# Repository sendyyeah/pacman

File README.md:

# pacman
40% Ortholinear Keyboard based on Raspberry RP2040

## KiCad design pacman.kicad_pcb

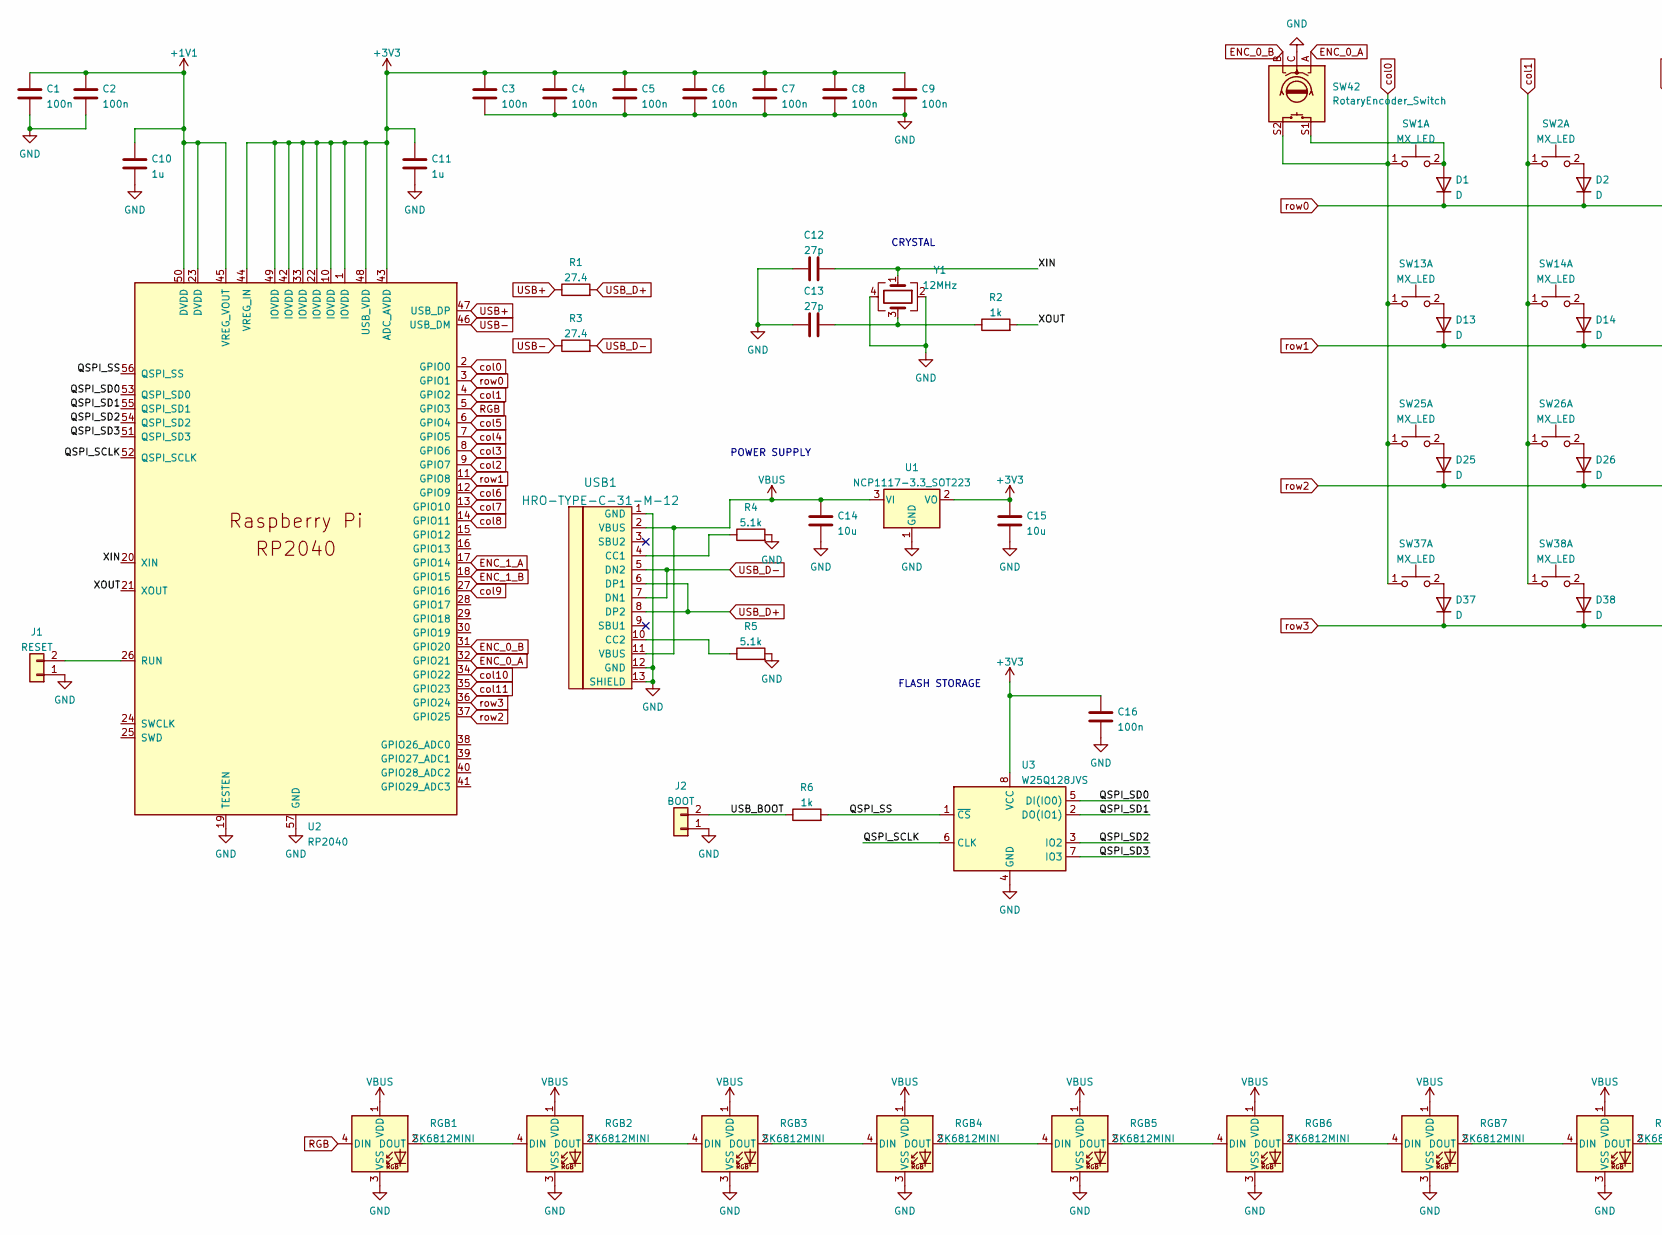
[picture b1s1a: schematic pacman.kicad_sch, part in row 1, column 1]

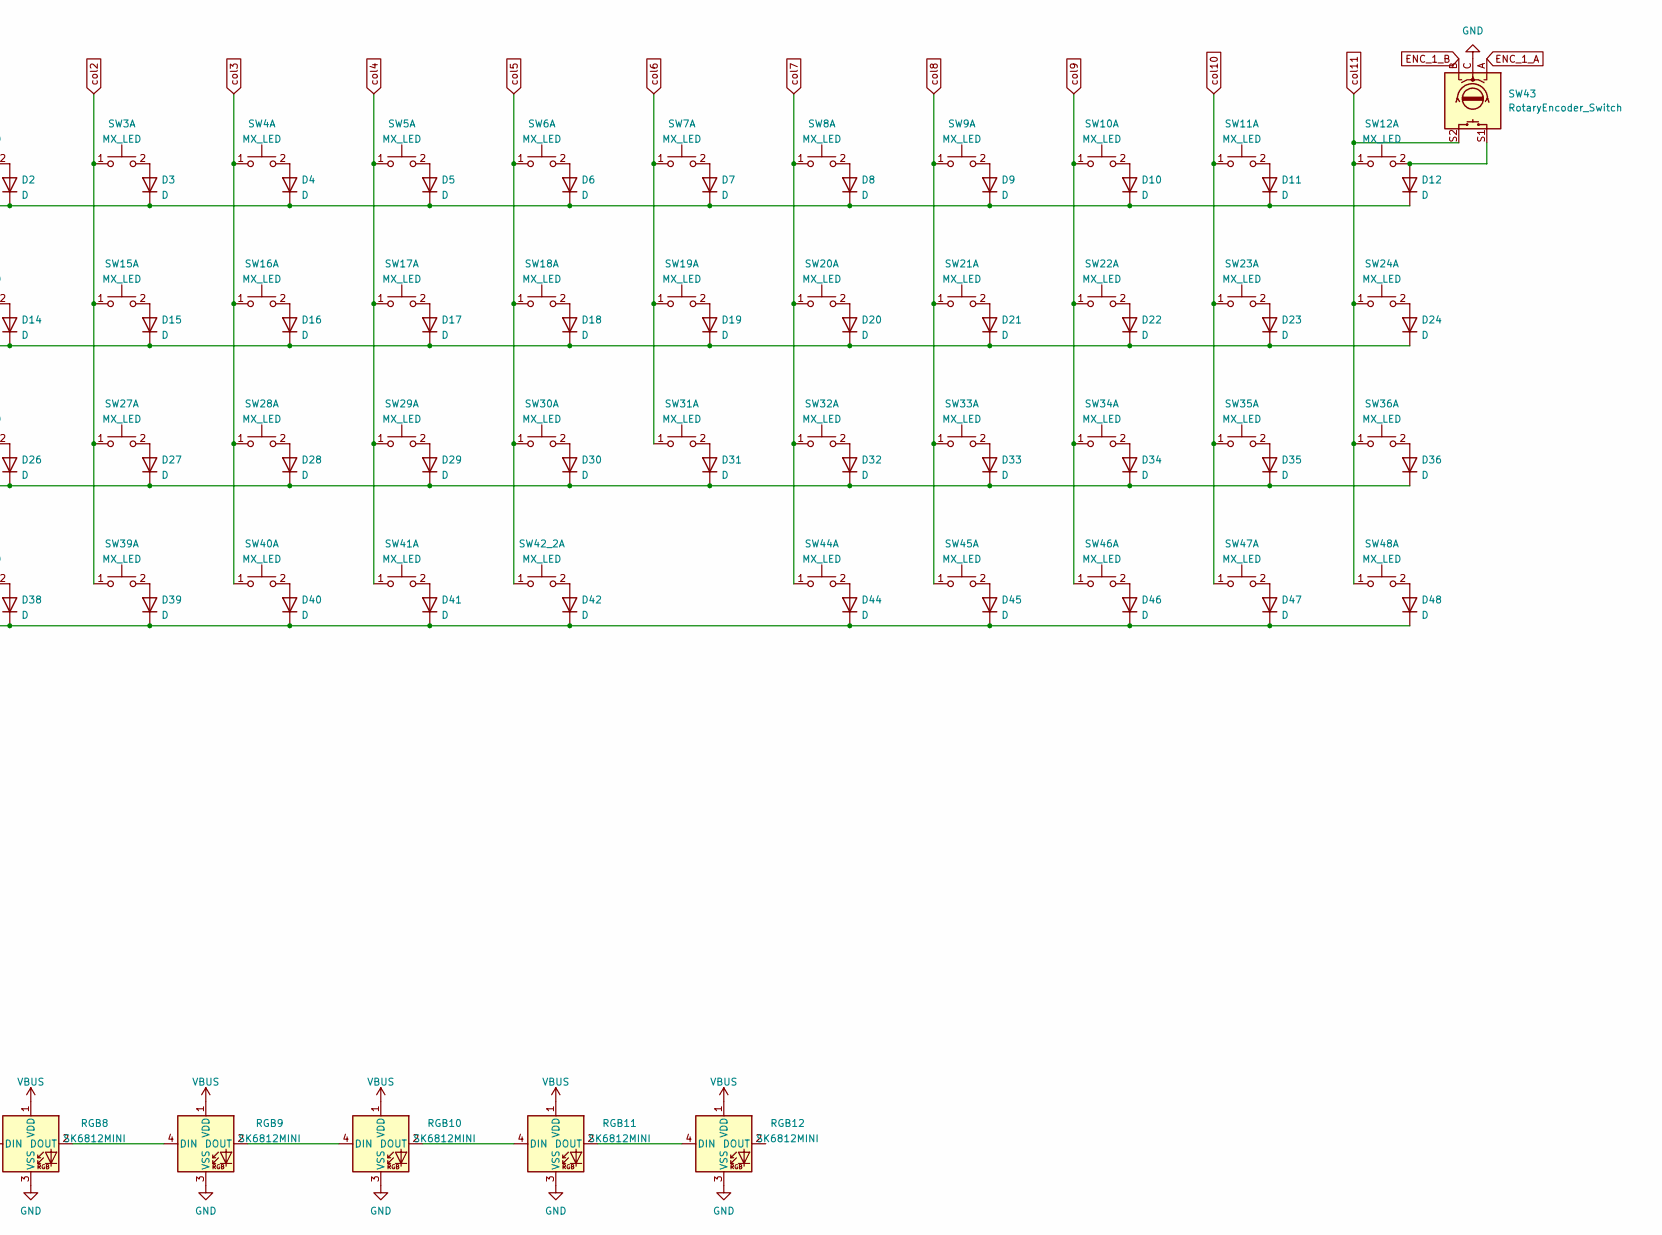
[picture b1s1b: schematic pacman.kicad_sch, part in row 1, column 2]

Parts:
C1, C2, C3, C4, C5, C6, C7, C8, C9, C16: 100n; C_0402_1005Metric
C10, C11: 1u; C_0402_1005Metric
C12, C13: 27p; C_0402_1005Metric
C14, C15: 10u; C_0402_1005Metric
D1, D2, D3, D4, D5, D6, D7, D8, D9, D10, D11, D12, D13, D14, D15, D16, D17, D18, D19, D20, D21, D22, D23, D24, D25, D26, D27, D28, D29, D30, D31, D32, D33, D34, D35, D36, D37, D38, D39, D40, D41, D42, D44, D45, D46, D47, D48: D; D_SOD-323
J1: RESET; SW_SPST_TL3342
J2: BOOT; SW_SPST_TL3342
R1, R3: 27.4; R_0402_1005Metric
R2, R6: 1k; R_0402_1005Metric
R4, R5: 5.1k; R_0402_1005Metric
RGB1, RGB2, RGB3, RGB4, RGB5, RGB6, RGB7, RGB8, RGB9, RGB10, RGB11, RGB12: SK6812MINI; LED_WS2812B_PLCC4_5.0x5.0mm_P3.2mm
SW1, SW2, SW3, SW4, SW5, SW6, SW7, SW8, SW9, SW10, SW11, SW12, SW13, SW14, SW15, SW16, SW17, SW18, SW19, SW20, SW21, SW22, SW23, SW24, SW25, SW26, SW27, SW28, SW29, SW30, SW31, SW32, SW33, SW34, SW35, SW36, SW37, SW38, SW39, SW40, SW41, SW44, SW45, SW46, SW47, SW48: MX_LED; MXOnly-1U-Hotswap
SW42, SW43: RotaryEncoder_Switch; RotaryEncoder_EC11
SW42_2: MX_LED; MXOnly-2U-Hotswap-ReversedStabilizers
U1: NCP1117-3.3_SOT223; SOT-223-3_TabPin2
U2: RP2040; RP2040-QFN-56
U3: W25Q128JVS; SOIC-8_5.23x5.23mm_P1.27mm
USB1: HRO-TYPE-C-31-M-12; HRO-TYPE-C-31-M-12-Assembly
Y1: 12MHz; Crystal_SMD_3225-4Pin_3.2x2.5mm_HandSoldering

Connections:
+1V1: C1.1, C2.1, C10.1, U2.23 (DVDD), U2.45 (VREG_VOUT), U2.50 (DVDD)
+3V3: C3.1, C4.1, C5.1, C6.1, C7.1, C8.1, C9.1, C11.1, C15.1, C16.1, U1.2 (VO), U2.1 (IOVDD), U2.10 (IOVDD), U2.22 (IOVDD), U2.33 (IOVDD), U2.42 (IOVDD), U2.43 (ADC_AVDD), U2.44 (VREG_IN), U2.48 (USB_VDD), U2.49 (IOVDD), U3.8 (VCC)
/QSPI_SCLK: U2.52 (QSPI_SCLK), U3.6 (CLK)
/QSPI_SD0: U2.53 (QSPI_SD0), U3.5 (DI(IO0))
/QSPI_SD1: U2.55 (QSPI_SD1), U3.2 (DO(IO1))
/QSPI_SD2: U2.54 (QSPI_SD2), U3.3 (IO2)
/QSPI_SD3: U2.51 (QSPI_SD3), U3.7 (IO3)
/QSPI_SS: R6.2, U2.56 (QSPI_SS), U3.1 (~CS)
/USB_BOOT: J2.2, R6.1
/XIN: C12.2, U2.20 (XIN), Y1.1
/XOUT: R2.2, U2.21 (XOUT)
ENC_0_A: SW42.A, U2.32 (GPIO21)
ENC_0_B: SW42.B, U2.31 (GPIO20)
ENC_1_A: SW43.A, U2.17 (GPIO14)
ENC_1_B: SW43.B, U2.18 (GPIO15)
GND: C1.2, C2.2, C3.2, C4.2, C5.2, C6.2, C7.2, C8.2, C9.2, C10.2, C11.2, C12.1, C13.1, C14.2, C15.2, C16.2, J1.1, J2.1, R4.2, R5.2, RGB1.3 (VSS), RGB2.3 (VSS), RGB3.3 (VSS), RGB4.3 (VSS), RGB5.3 (VSS), RGB6.3 (VSS), RGB7.3 (VSS), RGB8.3 (VSS), RGB9.3 (VSS), RGB10.3 (VSS), RGB11.3 (VSS), RGB12.3 (VSS), SW42.C, SW43.C, U1.1 (GND), U2.19 (TESTEN), U2.57 (GND), U3.4 (GND), USB1.1 (GND), USB1.12 (GND), USB1.13 (SHIELD), Y1.2, Y1.4
unnamed: C13.2, R2.1, Y1.3
unnamed: D1.2 (A), SW1.2, SW42.S1
unnamed: D2.2 (A), SW2.2
unnamed: D3.2 (A), SW3.2
unnamed: D4.2 (A), SW4.2
unnamed: D5.2 (A), SW5.2
unnamed: D6.2 (A), SW6.2
unnamed: D7.2 (A), SW7.2
unnamed: D8.2 (A), SW8.2
unnamed: D9.2 (A), SW9.2
unnamed: D10.2 (A), SW10.2
unnamed: D11.2 (A), SW11.2
unnamed: D12.2 (A), SW12.2, SW43.S1
unnamed: D13.2 (A), SW13.2
unnamed: D14.2 (A), SW14.2
unnamed: D15.2 (A), SW15.2
unnamed: D16.2 (A), SW16.2
unnamed: D17.2 (A), SW17.2
unnamed: D18.2 (A), SW18.2
unnamed: D19.2 (A), SW19.2
unnamed: D20.2 (A), SW20.2
unnamed: D21.2 (A), SW21.2
unnamed: D22.2 (A), SW22.2
unnamed: D23.2 (A), SW23.2
unnamed: D24.2 (A), SW24.2
unnamed: D25.2 (A), SW25.2
unnamed: D26.2 (A), SW26.2
unnamed: D27.2 (A), SW27.2
unnamed: D28.2 (A), SW28.2
unnamed: D29.2 (A), SW29.2
unnamed: D30.2 (A), SW30.2
unnamed: D31.2 (A), SW31.2
unnamed: D32.2 (A), SW32.2
unnamed: D33.2 (A), SW33.2
unnamed: D34.2 (A), SW34.2
unnamed: D35.2 (A), SW35.2
unnamed: D36.2 (A), SW36.2
unnamed: D37.2 (A), SW37.2
unnamed: D38.2 (A), SW38.2
unnamed: D39.2 (A), SW39.2
unnamed: D40.2 (A), SW40.2
unnamed: D41.2 (A), SW41.2
unnamed: D42.2 (A), SW42_2.2
unnamed: D44.2 (A), SW44.2
unnamed: D45.2 (A), SW45.2
unnamed: D46.2 (A), SW46.2
unnamed: D47.2 (A), SW47.2
unnamed: D48.2 (A), SW48.2
unnamed: J1.2, U2.26 (RUN)
unnamed: RGB1.2 (DOUT), RGB2.4 (DIN)
unnamed: RGB2.2 (DOUT), RGB3.4 (DIN)
unnamed: RGB3.2 (DOUT), RGB4.4 (DIN)
unnamed: RGB4.2 (DOUT), RGB5.4 (DIN)
unnamed: RGB5.2 (DOUT), RGB6.4 (DIN)
unnamed: RGB6.2 (DOUT), RGB7.4 (DIN)
unnamed: RGB7.2 (DOUT), RGB8.4 (DIN)
unnamed: RGB8.2 (DOUT), RGB9.4 (DIN)
unnamed: RGB9.2 (DOUT), RGB10.4 (DIN)
unnamed: RGB10.2 (DOUT), RGB11.4 (DIN)
unnamed: RGB11.2 (DOUT), RGB12.4 (DIN)
unnamed: R4.1, USB1.4 (CC1)
unnamed: R5.1, USB1.10 (CC2)
RGB: RGB1.4 (DIN), U2.5 (GPIO3)
USB+: R1.1, U2.47 (USB_DP)
USB-: R3.1, U2.46 (USB_DM)
USB_D+: R1.2, USB1.6 (DP1), USB1.8 (DP2)
USB_D-: R3.2, USB1.5 (DN2), USB1.7 (DN1)
VBUS: C14.1, RGB1.1 (VDD), RGB2.1 (VDD), RGB3.1 (VDD), RGB4.1 (VDD), RGB5.1 (VDD), RGB6.1 (VDD), RGB7.1 (VDD), RGB8.1 (VDD), RGB9.1 (VDD), RGB10.1 (VDD), RGB11.1 (VDD), RGB12.1 (VDD), U1.3 (VI), USB1.2 (VBUS), USB1.11 (VBUS)
col0: SW1.1, SW13.1, SW25.1, SW37.1, SW42.S2, U2.2 (GPIO0)
col1: SW2.1, SW14.1, SW26.1, SW38.1, U2.4 (GPIO2)
col2: SW3.1, SW15.1, SW27.1, SW39.1, U2.9 (GPIO7)
col3: SW4.1, SW16.1, SW28.1, SW40.1, U2.8 (GPIO6)
col4: SW5.1, SW17.1, SW29.1, SW41.1, U2.7 (GPIO5)
col5: SW6.1, SW18.1, SW30.1, SW42_2.1, U2.6 (GPIO4)
col6: SW7.1, SW19.1, SW31.1, U2.12 (GPIO9)
col7: SW8.1, SW20.1, SW32.1, SW44.1, U2.13 (GPIO10)
col8: SW9.1, SW21.1, SW33.1, SW45.1, U2.14 (GPIO11)
col9: SW10.1, SW22.1, SW34.1, SW46.1, U2.27 (GPIO16)
col10: SW11.1, SW23.1, SW35.1, SW47.1, U2.34 (GPIO22)
col11: SW12.1, SW24.1, SW36.1, SW43.S2, SW48.1, U2.35 (GPIO23)
row0: D1.1 (K), D2.1 (K), D3.1 (K), D4.1 (K), D5.1 (K), D6.1 (K), D7.1 (K), D8.1 (K), D9.1 (K), D10.1 (K), D11.1 (K), D12.1 (K), U2.3 (GPIO1)
row1: D13.1 (K), D14.1 (K), D15.1 (K), D16.1 (K), D17.1 (K), D18.1 (K), D19.1 (K), D20.1 (K), D21.1 (K), D22.1 (K), D23.1 (K), D24.1 (K), U2.11 (GPIO8)
row2: D25.1 (K), D26.1 (K), D27.1 (K), D28.1 (K), D29.1 (K), D30.1 (K), D31.1 (K), D32.1 (K), D33.1 (K), D34.1 (K), D35.1 (K), D36.1 (K), U2.37 (GPIO25)
row3: D37.1 (K), D38.1 (K), D39.1 (K), D40.1 (K), D41.1 (K), D42.1 (K), D44.1 (K), D45.1 (K), D46.1 (K), D47.1 (K), D48.1 (K), U2.36 (GPIO24)

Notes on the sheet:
CRYSTAL
FLASH STORAGE
POWER SUPPLY

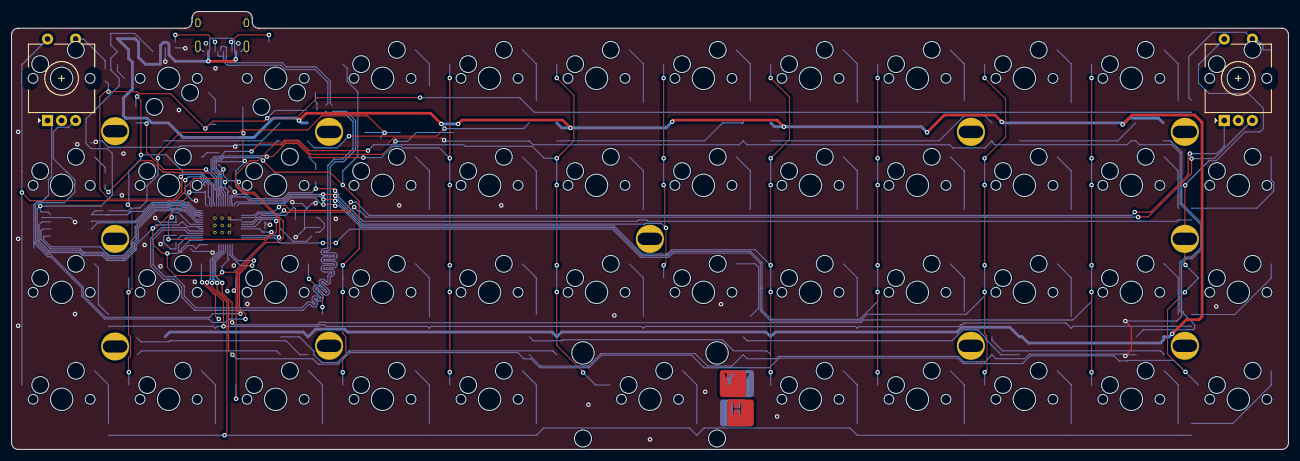
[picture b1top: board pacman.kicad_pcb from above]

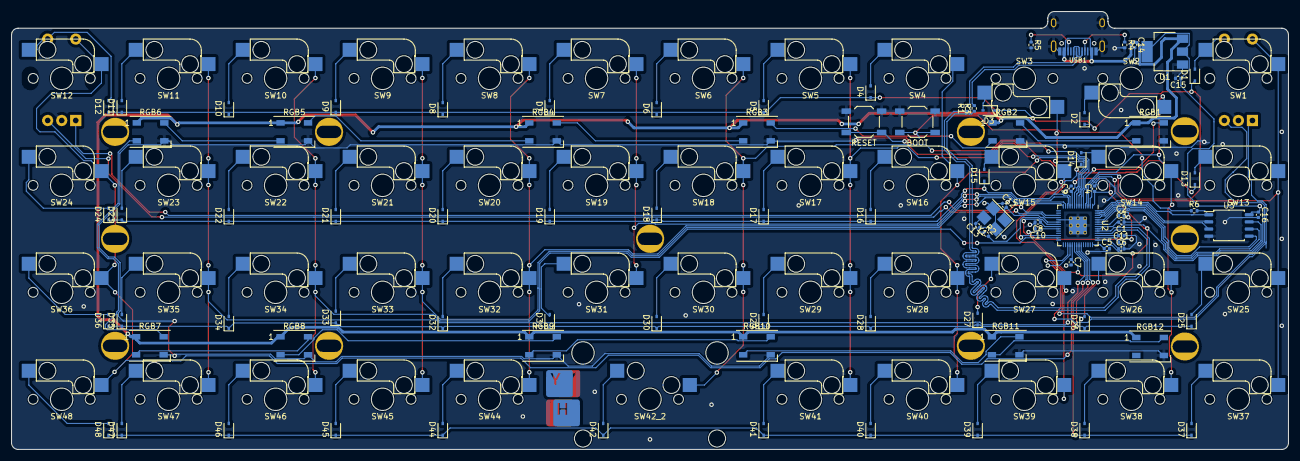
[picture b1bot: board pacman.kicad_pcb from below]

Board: 2 copper layers, 227.4 x 78.0 mm, 139 parts (89 on the bottom side), 100 nets.

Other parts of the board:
Ref**: Val**; yh
Ref**#2: Val**; yh

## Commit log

2023-09-30 Fix unconnected rows
2023-09-30 Fix unconnected Column
2023-10-01 Add initial backup
2024-01-11 Add Encoder
2024-01-11 fix fill
